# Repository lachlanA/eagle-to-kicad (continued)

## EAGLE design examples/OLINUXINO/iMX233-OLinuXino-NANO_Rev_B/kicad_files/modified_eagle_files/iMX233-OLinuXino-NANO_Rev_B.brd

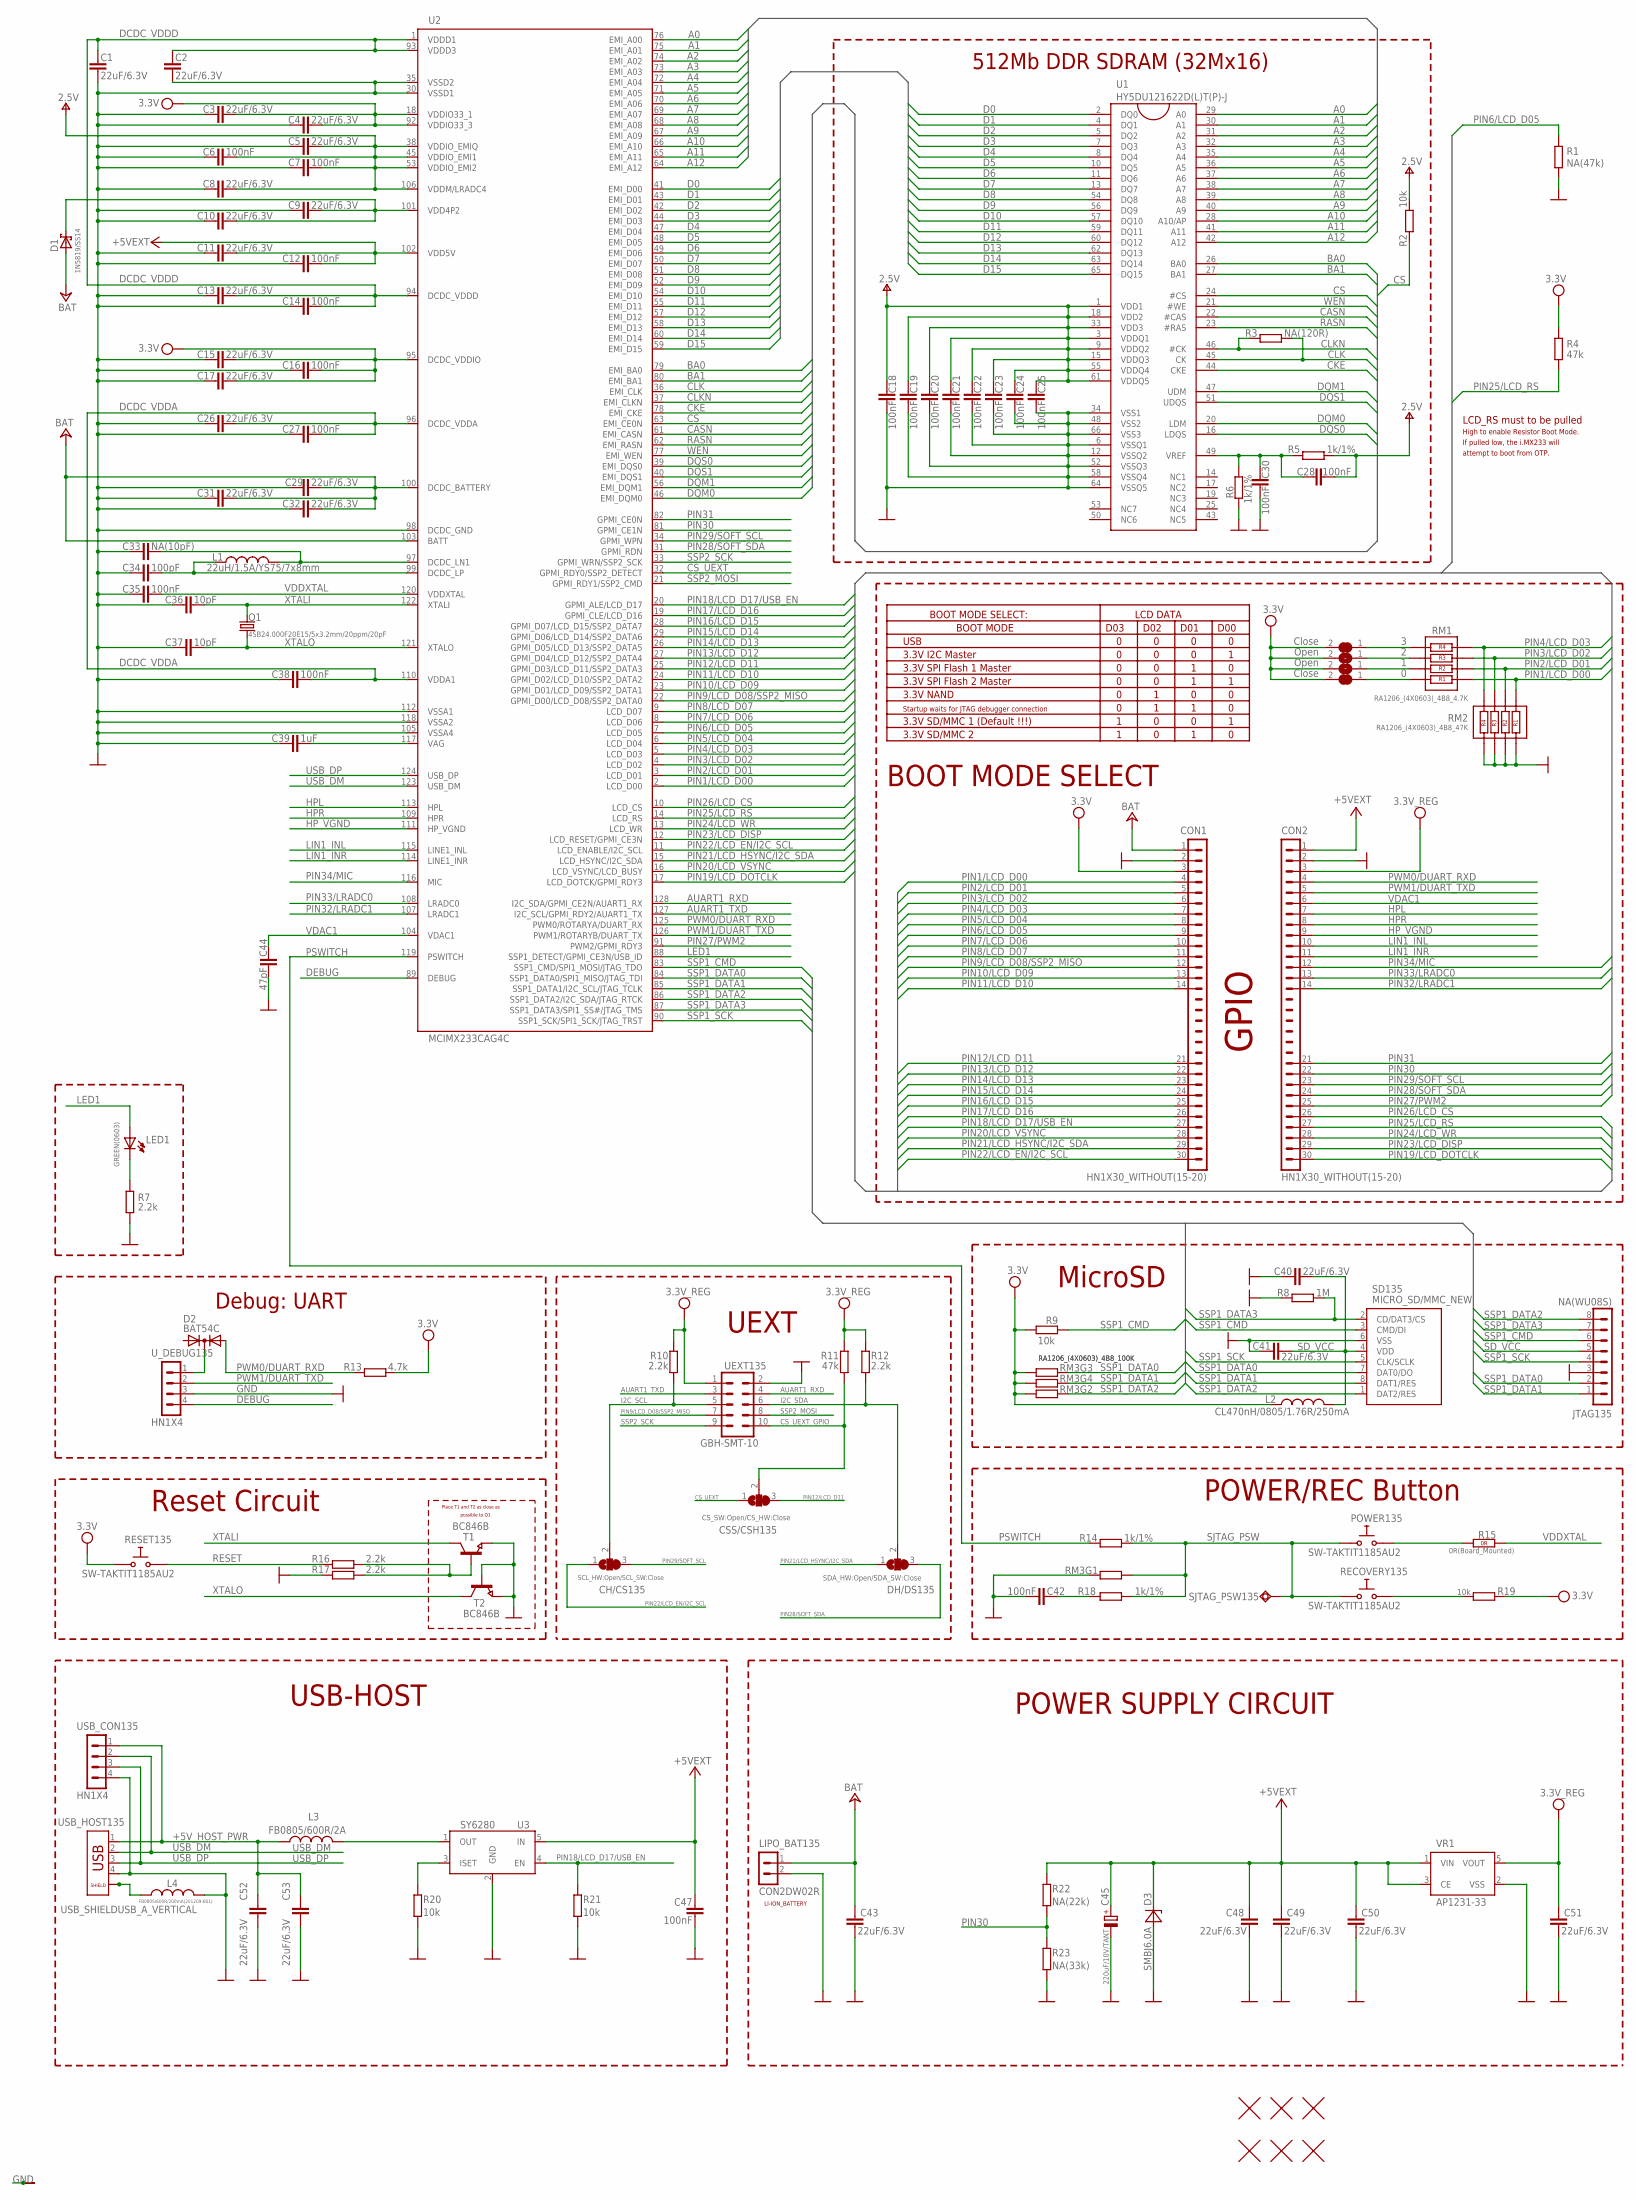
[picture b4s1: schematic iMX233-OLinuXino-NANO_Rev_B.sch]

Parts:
0, 3: Close; SJ_1_SMALLER
1, 2: Open; SJ_1_SMALLER
C1, C2, C3, C4, C5, C8, C9, C10, C11, C13, C15, C17, C26, C29, C31, C32, C40, C41, C43, C48, C49, C50, C51, C52, C53: 22uF/6.3V; C0603_DWS
C6, C7, C12, C14, C16, C18, C19, C20, C21, C22, C23, C24, C25, C27, C28, C30, C35, C38, C42: 100nF; C0402_TI
C33: NA(10pF); C0603_DWS
C34: 100pF; C0603_DWS
C36, C37: 10pF; C0603_DWS
C39: 1uF; C0603_DWS
C44: 47pF; C0603_DWS
C45: 220uF/10V/TANT; CT7343
C47: 100nF; C0603_DWS
CH/CS135: SCL_HW:Open/SCL_SW:Close; SJ_2_SMALLER
CON1, CON2: HN1X30_WITHOUT(15-20)
CSS/CSH135: CS_SW:Open/CS_HW:Close; SJ_2_SMALLER
D1: 1N5819/SS14; MLL-41
D2: BAT54C; SOT23C
D3: SMBJ6.0A; DO214AA
DH/DS135: SDA_HW:Open/SDA_SW:Close; SJ_2_SMALLER
JTAG135: NA(WU08S); WU08S
L1: 22uH/1.5A/YS75/7x8mm; L7078
L2: CL470nH/0805/1.76R/250mA; L0805_5MIL_DWS
L3: FB0805/600R/2A; L0805_5MIL_DWS
L4: FB0805/600R/200mA(201209-601); L0805_5MIL_DWS
LED1: GREEN(0603); LED-0603
LIPO_BAT135: CON2DW02R; DW02R
POWER135: SW-TAKTIT1185AU2; IT1185AU2
Q1: 4SB24.000F20E15/5x3.2mm/20ppm/20pF; HCX-4S
R1: NA(47k); R0603_5MIL_DWS
R2, R9, R19, R20, R21: 10k; R0603_5MIL_DWS
R3: NA(120R); R0603_5MIL_DWS
R4, R11: 47k; R0603_5MIL_DWS
R5, R6, R14, R18: 1k/1%; R0603_5MIL_DWS
R7, R10, R12, R16, R17: 2.2k; R0603_5MIL_DWS
R8: 1M; R0603_5MIL_DWS
R13: 4.7k; R0603_5MIL_DWS
R15: 0R(Board_Mounted); 0603_0R
R22: NA(22k); R0603_5MIL_DWS
R23: NA(33k); R0603_5MIL_DWS
RECOVERY135: SW-TAKTIT1185AU2; IT1185AU2
RESET135: SW-TAKTIT1185AU2; IT1185AU2
RM1: RA1206_(4X0603)_4B8_4.7K; R_MATRIX_4
RM2: RA1206_(4X0603)_4B8_47K; R_MATRIX_4
RM3: RA1206_(4X0603)_4B8_100K; R_MATRIX_4
SD135: MICRO_SD/MMC_NEW; TFR/C-MEM-CON
SJTAG_PSW135: TESTPAD40/70; TESTPAD
T1, T2: BC846B; SOT23
U1: HY5DU121622D(L)T(P)-J; 66TSOP-II
U2: MCIMX233CAG4C; TQFP128LD
U3: SY6280; SOT23-5
U$1, U$2, U$3, U$7, U$13, U$14: FIDUCIAL1X2; FIDUCIAL-1X2
UEXT135: GBH-SMT-10; ML10_S
USB_CON135: HN1X4
USB_HOST135: USB_SHIELDUSB_A_VERTICAL; USB_A_VERTICAL_PTH
U_DEBUG135: HN1X4
VP_0: VPDEV0; VPAC0
VP_1, VP_2, VP_3, VP_4, VP_5, VP_6, VP_7: VPDEV1; VPAC1
VR1: AP1231-33; SOT-23-5

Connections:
+5V: C11.2, C12.2, C45.+, C47.1, C48.1, C49.1, C50.1, CON2.1, D3.C, R22.2, U2.102 (VDD5V), U3.5 (IN), VR1.1 (VIN), VR1.3 (CE)
+5V_HOST_PWR: C52.1, C53.1, L3.1, USB_CON135.1, USB_HOST135.1
+24V: C29.2, C31.2, C32.2, C43.1, CON1.1, D1.A, LIPO_BAT135.1, U2.100 (DCDC_BATTERY), U2.103 (BATT)
A0: U1.29 (A0), U2.76 (EMI_A00)
A1: U1.30 (A1), U2.75 (EMI_A01)
A2: U1.31 (A2), U2.74 (EMI_A02)
A3: U1.32 (A3), U2.73 (EMI_A03)
A4: U1.35 (A4), U2.72 (EMI_A04)
A5: U1.36 (A5), U2.71 (EMI_A05)
A6: U1.37 (A6), U2.70 (EMI_A06)
A7: U1.38 (A7), U2.69 (EMI_A07)
A8: U1.39 (A8), U2.68 (EMI_A08)
A9: U1.40 (A9), U2.67 (EMI_A09)
A10: U1.28 (A10/AP), U2.66 (EMI_A10)
A11: U1.41 (A11), U2.65 (EMI_A11)
A12: U1.42 (A12), U2.64 (EMI_A12)
AUART1_RXD: U2.128 (I2C_SDA/GPMI_CE2N/AUART1_RX), UEXT135.4
AUART1_TXD: U2.127 (I2C_SCL/GPMI_RDY2/AUART1_TX), UEXT135.3
BA0: U1.26 (BA0), U2.79 (EMI_BA0)
BA1: U1.27 (BA1), U2.80 (EMI_BA1)
CASN: U1.22 (#CAS), U2.61 (EMI_CASN)
CKE: U1.44 (CKE), U2.78 (EMI_CKE)
CLK: R3.2, U1.45 (CK), U2.36 (EMI_CLK)
CLKN: R3.1, U1.46 (#CK), U2.37 (EMI_CLKN)
CS: R2.1, U1.24 (#CS), U2.63 (EMI_CE0N)
CS_UEXT: CSS/CSH135.1, U2.32 (GPMI_RDY0/SSP2_DETECT)
CS_UEXT_GPIO: CSS/CSH135.2, R11.1, UEXT135.10
D0: U1.2 (DQ0), U2.41 (EMI_D00)
D1: U1.4 (DQ1), U2.43 (EMI_D01)
D2: U1.5 (DQ2), U2.42 (EMI_D02)
D3: U1.7 (DQ3), U2.44 (EMI_D03)
D4: U1.8 (DQ4), U2.47 (EMI_D04)
D5: U1.10 (DQ5), U2.48 (EMI_D05)
D6: U1.11 (DQ6), U2.49 (EMI_D06)
D7: U1.13 (DQ7), U2.50 (EMI_D07)
D8: U1.54 (DQ8), U2.51 (EMI_D08)
D9: U1.56 (DQ9), U2.52 (EMI_D09)
D10: U1.57 (DQ10), U2.54 (EMI_D10)
D11: U1.59 (DQ11), U2.55 (EMI_D11)
D12: U1.60 (DQ12), U2.57 (EMI_D12)
D13: U1.62 (DQ13), U2.58 (EMI_D13)
D14: U1.63 (DQ14), U2.60 (EMI_D14)
D15: U1.65 (DQ15), U2.59 (EMI_D15)
DCDC_VDDA: C26.2, C27.2, C38.2, U2.96 (DCDC_VDDA), U2.110 (VDDA1)
DCDC_VDDD: C1.2, C2.2, C13.2, C14.2, U2.1 (VDDD1), U2.93 (VDDD3), U2.94 (DCDC_VDDD)
DEBUG: U2.89 (DEBUG), U_DEBUG135.4
DQM0: U1.20 (LDM), U2.46 (EMI_DQM0)
DQM1: U1.47 (UDM), U2.56 (EMI_DQM1)
DQS0: U1.16 (LDQS), U2.39 (EMI_DQS0)
DQS1: U1.51 (UDQS), U2.40 (EMI_DQS1)
GND: C1.1, C2.1, C3.1, C4.1, C5.1, C6.1, C7.1, C8.1, C9.1, C10.1, C11.1, C12.1, C13.1, C14.1, C15.1, C16.1, C17.1, C18.1, C19.1, C20.1, C21.1, C22.1, C23.1, C24.1, C25.1, C26.1, C27.1, C29.1, C30.1, C31.1, C32.1, C33.1, C34.1, C35.1, C36.1, C37.1, C38.1, C39.1, C40.1, C41.1, C42.2, C43.2, C44.2, C45.-, C47.2, C48.2, C49.2, C50.2, C51.2, C52.2, C53.2, CON1.2, CON2.2, D3.A, JTAG135.3, L4.1, LIPO_BAT135.2, R1.1, R6.1, R7.1, R8.2, R17.2, R20.1, R21.1, R23.1, RM2.1.2, RM2.2.2, RM2.3.2, RM2.4.2, RM3.1.1 (1), SD135.6 (VSS), T1.2 (E), T2.1 (B), T2.2 (E), U1.6 (VSSQ1), U1.12 (VSSQ2), U1.34 (VSS1), U1.48 (VSS2), U1.52 (VSSQ3), U1.58 (VSSQ4), U1.64 (VSSQ5), U1.66 (VSS3), U2.30 (VSSD1), U2.35 (VSSD2), U2.98 (DCDC_GND), U2.105 (VSSA4), U2.112 (VSSA1), U2.118 (VSSA2), U3.2 (GND), UEXT135.2, USB_CON135.4, USB_HOST135.4, U_DEBUG135.3, VP_0.VP, VP_1.VP, VP_2.VP, VP_3.VP, VP_4.VP, VP_5.VP, VP_6.VP, VP_7.VP, VR1.2 (VSS)
HPL: CON2.7, U2.113 (HPL)
HPR: CON2.8, U2.109 (HPR)
HP_VGND: CON2.9, U2.111 (HP_VGND)
I2C_SCL: CH/CS135.2, R10.1, UEXT135.5
I2C_SDA: DH/DS135.2, R12.1, UEXT135.6
LED1: LED1.A, U2.88 (SSP1_DETECT/GPMI_CE3N/USB_ID)
LIN1_INL: CON2.10, U2.115 (LINE1_INL)
LIN1_INR: CON2.11, U2.114 (LINE1_INR)
unnamed: POWER135.1 (0), R15.1 (1.1)
unnamed: L3.2, U3.1 (OUT)
unnamed: R20.2, U3.3 (ISET)
unnamed: C28.2, C30.2, R5.1, R6.2, U1.49 (VREF)
unnamed: R19.1, RECOVERY135.1 (0)
unnamed: D2.3 (K), U_DEBUG135.1
unnamed: C33.2, L1.2, U2.97 (DCDC_LN1)
unnamed: C34.2, L1.1, U2.99 (DCDC_LP)
unnamed: C39.2, U2.117 (VAG)
unnamed: C42.1, R18.1
unnamed: LED1.C, R7.2
unnamed: R16.1, R17.1, T1.1 (B)
unnamed: 3.1, RM1.4.1
unnamed: 2.1, RM1.3.1
unnamed: 1.1, RM1.2.1
unnamed: 0.1, RM1.1.1
unnamed: L4.2, USB_HOST135.P$3 (5), USB_HOST135.P$4 (6)
PIN1/LCD_D00: CON1.4, RM1.1.2, RM2.1.1, U2.2 (LCD_D00)
PIN2/LCD_D01: CON1.5, RM1.2.2, RM2.2.1, U2.3 (LCD_D01)
PIN3/LCD_D02: CON1.6, RM1.3.2, RM2.3.1, U2.4 (LCD_D02)
PIN4/LCD_D03: CON1.7, RM1.4.2, RM2.4.1, U2.5 (LCD_D03)
PIN5/LCD_D04: CON1.8, U2.6 (LCD_D04)
PIN6/LCD_D05: CON1.9, R1.2, U2.7 (LCD_D05)
PIN7/LCD_D06: CON1.10, U2.8 (LCD_D06)
PIN8/LCD_D07: CON1.11, U2.9 (LCD_D07)
PIN9/LCD_D08/SSP2_MISO: CON1.12, U2.22 (GPMI_D00/LCD_D08/SSP2_DATA0), UEXT135.7
PIN10/LCD_D09: CON1.13, U2.23 (GPMI_D01/LCD_D09/SSP2_DATA1)
PIN11/LCD_D10: CON1.14, U2.24 (GPMI_D02/LCD_D10/SSP2_DATA2)
PIN12/LCD_D11: CON1.21, CSS/CSH135.3, U2.25 (GPMI_D03/LCD_D11/SSP2_DATA3)
PIN13/LCD_D12: CON1.22, U2.27 (GPMI_D04/LCD_D12/SSP2_DATA4)
PIN14/LCD_D13: CON1.23, U2.26 (GPMI_D05/LCD_D13/SSP2_DATA5)
PIN15/LCD_D14: CON1.24, U2.29 (GPMI_D06/LCD_D14/SSP2_DATA6)
PIN16/LCD_D15: CON1.25, U2.28 (GPMI_D07/LCD_D15/SSP2_DATA7)
PIN17/LCD_D16: CON1.26, U2.19 (GPMI_CLE/LCD_D16)
PIN18/LCD_D17/USB_EN: CON1.27, R21.2, U2.20 (GPMI_ALE/LCD_D17), U3.4 (EN)
PIN19/LCD_DOTCLK: CON2.30, U2.17 (LCD_DOTCK/GPMI_RDY3)
PIN20/LCD_VSYNC: CON1.28, U2.16 (LCD_VSYNC/LCD_BUSY)
PIN21/LCD_HSYNC/I2C_SDA: CON1.29, DH/DS135.1, U2.15 (LCD_HSYNC/I2C_SDA)
PIN22/LCD_EN/I2C_SCL: CH/CS135.1, CON1.30, U2.11 (LCD_ENABLE/I2C_SCL)
PIN23/LCD_DISP: CON2.29, U2.12 (LCD_RESET/GPMI_CE3N)
PIN24/LCD_WR: CON2.28, U2.13 (LCD_WR)
PIN25/LCD_RS: CON2.27, R4.2, U2.14 (LCD_RS)
PIN26/LCD_CS: CON2.26, U2.10 (LCD_CS)
PIN27/PWM2: CON2.25, U2.91 (PWM2/GPMI_RDY3)
PIN28/SOFT_SDA: CON2.24, DH/DS135.3, U2.31 (GPMI_RDN)
PIN29/SOFT_SCL: CH/CS135.3, CON2.23, U2.34 (GPMI_WPN)
PIN30: CON2.22, R22.1, R23.2, U2.81 (GPMI_CE1N)
PIN31: CON2.21, U2.82 (GPMI_CE0N)
PIN32/LRADC1: CON2.14, U2.107 (LRADC1)
PIN33/LRADC0: CON2.13, U2.108 (LRADC0)
PIN34/MIC: CON2.12, U2.116 (MIC)
PSWITCH: R14.1, U2.119 (PSWITCH)
PWM0/DUART_RXD: CON2.4, D2.2 (A2), R13.2, U2.125 (PWM0/ROTARYA/DUART_RX)
PWM1/DUART_TXD: CON2.5, U2.126 (PWM1/ROTARYB/DUART_TX), U_DEBUG135.2
RASN: U1.23 (#RAS), U2.62 (EMI_RASN)
RESET: R16.2, RESET135.1 (0)
SD_VCC: C40.2, C41.2, JTAG135.5, L2.2, SD135.4 (VDD)
SJTAG_PSW: POWER135.2 (1), R14.2, R18.2, RECOVERY135.2 (1), RM3.1.2 (2), SJTAG_PSW135.P$1
SSP1_CMD: JTAG135.6, R9.1, SD135.3 (CMD/DI), U2.83 (SSP1_CMD/SPI1_MOSI/JTAG_TDO)
SSP1_DATA0: JTAG135.2, RM3.3.2 (2), SD135.7 (DAT0/DO), U2.84 (SSP1_DATA0/SPI1_MISO/JTAG_TDI)
SSP1_DATA1: JTAG135.1, RM3.4.2 (2), SD135.8 (DAT1/RES), U2.85 (SSP1_DATA1/I2C_SCL/JTAG_TCLK)
SSP1_DATA2: JTAG135.8, RM3.2.2 (2), SD135.1 (DAT2/RES), U2.86 (SSP1_DATA2/I2C_SDA/JTAG_RTCK)
SSP1_DATA3: JTAG135.7, R8.1, SD135.2 (CD/DAT3/CS), U2.87 (SSP1_DATA3/SPI1_SS#/JTAG_TMS)
SSP1_SCK: JTAG135.4, SD135.5 (CLK/SCLK), U2.90 (SSP1_SCK/SPI1_SCK/JTAG_TRST)
SSP2_MOSI: U2.21 (GPMI_RDY1/SSP2_CMD), UEXT135.8
SSP2_SCK: U2.33 (GPMI_WRN/SSP2_SCK), UEXT135.9
USB_DM: U2.123 (USB_DM), USB_CON135.2, USB_HOST135.2
USB_DP: U2.124 (USB_DP), USB_CON135.3, USB_HOST135.3
V+: C5.2, C6.2, C7.2, C8.2, C18.2, C19.2, C20.2, C21.2, C22.2, C23.2, C24.2, C25.2, C28.1, R2.2, R5.2, U1.1 (VDD1), U1.3 (VDDQ1), U1.9 (VDDQ2), U1.15 (VDDQ3), U1.18 (VDD2), U1.33 (VDD3), U1.55 (VDDQ4), U1.61 (VDDQ5), U2.38 (VDDIO_EMIQ), U2.45 (VDDIO_EMI1), U2.53 (VDDIO_EMI2), U2.106 (VDDM/LRADC4)
VCC: 0.2, 1.2, 2.2, 3.2, C3.2, C4.2, C15.2, C16.2, C17.2, CON1.3, L2.1, R4.1, R9.2, R13.1, R19.2, RESET135.2 (1), RM3.2.1 (1), RM3.3.1 (1), RM3.4.1 (1), U2.18 (VDDIO33_1), U2.92 (VDDIO33_3), U2.95 (DCDC_VDDIO)
VDAC1: C44.1, CON2.6, U2.104 (VDAC1)
VDD4P2: C9.2, C10.2, D1.K (C), U2.101 (VDD4P2)
VDDXTAL: C35.2, R15.2 (1.2), U2.120 (VDDXTAL)
VPP: C51.1, CON2.3, R10.2, R11.2, R12.2, UEXT135.1, VR1.5 (VOUT)
WEN: U1.21 (#WE), U2.77 (EMI_WEN)
XTALI: C36.2, Q1.2, T1.3 (C), U2.122 (XTALI)
XTALO: C37.2, Q1.1, T2.3 (C), U2.121 (XTALO)

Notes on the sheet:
POWER SUPPLY CIRCUIT
Place T1 and T2 as close as
possible to Q1
Reset Circuit
512Mb DDR SDRAM (32Mx16)
MicroSD
POWER/REC Button
BOOT MODE SELECT
BOOT MODE SELECT:
LCD DATA
BOOT MODE
D03
D02
D01
D00
USB
3.3V I2C Master
3.3V SPI Flash 1 Master
3.3V SPI Flash 2 Master
3.3V NAND
Startup waits for JTAG debugger connection
3.3V SD/MMC 1 (Default !!!)
3.3V SD/MMC 2
LCD_RS must to be pulled
High to enable Resistor Boot Mode.
If pulled low, the i.MX233 will
attempt to boot from OTP.
GPIO
Debug: UART
UEXT
USB-HOST
LI-ION_BATTERY

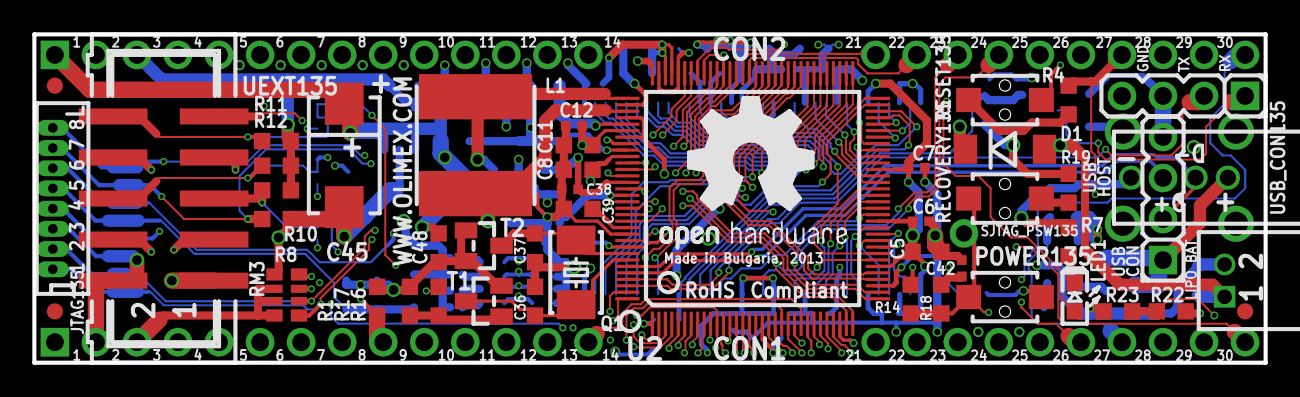
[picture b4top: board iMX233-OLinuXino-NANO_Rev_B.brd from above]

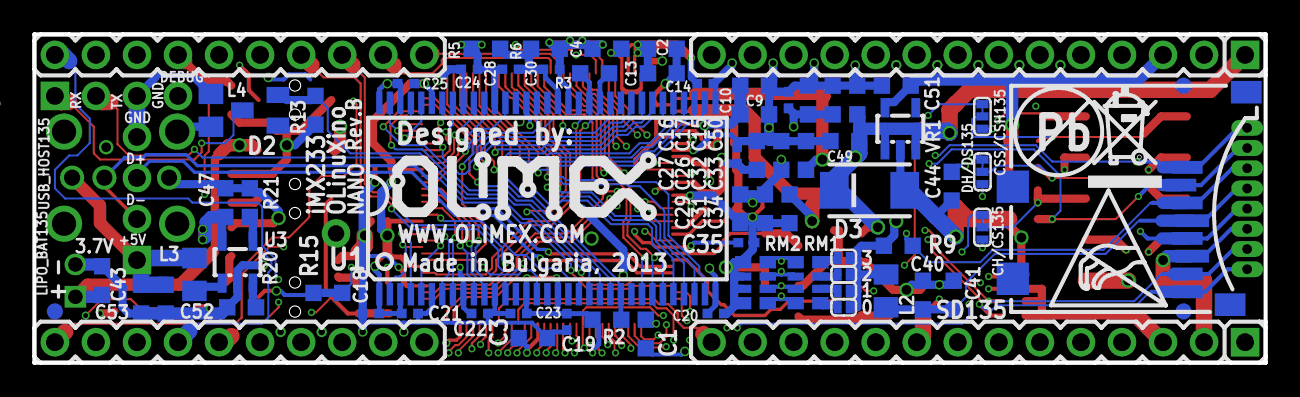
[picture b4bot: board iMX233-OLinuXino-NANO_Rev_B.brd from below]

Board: 6 copper layers, 76.2 x 20.3 mm, 132 parts (75 on the bottom side), 136 nets.

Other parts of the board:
U$4: ESD_SYMBOL
U$6: RECYCLE_BIN1/8
U$8: OLIMEX1_V
U$15: PB
U$18: LOGO-OPENHARDWARE_8X8
